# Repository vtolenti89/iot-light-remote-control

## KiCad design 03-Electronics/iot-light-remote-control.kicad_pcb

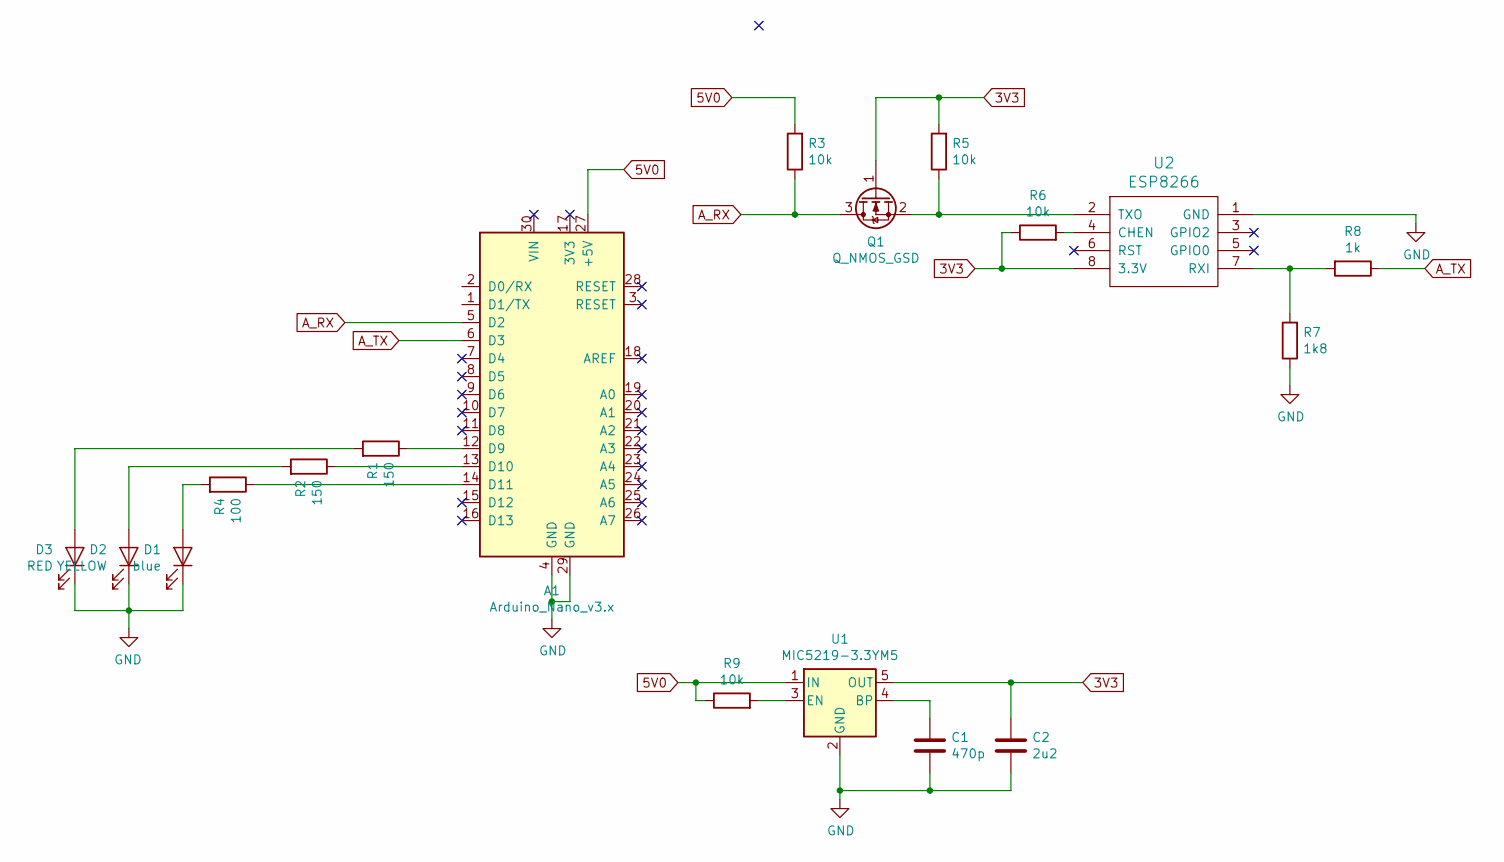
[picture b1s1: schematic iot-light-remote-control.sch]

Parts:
A1: Arduino_Nano_v3.x; Arduino_Nano
C1: 470p; C_0603_1608Metric_Pad1.05x0.95mm_HandSolder
C2: 2u2; C_0603_1608Metric_Pad1.05x0.95mm_HandSolder
D1: blue; LED_D5.0mm
D2: YELLOW; LED_D5.0mm
D3: RED; LED_D5.0mm
Q1: Q_NMOS_GSD; SOT-23
R1, R2: 150; R_0603_1608Metric_Pad1.05x0.95mm_HandSolder
R3, R5, R6, R9: 10k; R_0603_1608Metric_Pad1.05x0.95mm_HandSolder
R4: 100; R_0603_1608Metric_Pad1.05x0.95mm_HandSolder
R7: 1k8; R_0603_1608Metric_Pad1.05x0.95mm_HandSolder
R8: 1k; R_0603_1608Metric_Pad1.05x0.95mm_HandSolder
U1: MIC5219-3.3YM5; SOT-23-5
U2: ESP8266; PinHeader_2x04_P2.54mm_Vertical

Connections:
3V3: C2.1, Q1.1 (G), R5.2, R6.1, U1.5 (OUT), U2.8 (3.3V)
5V0: A1.27 (+5V), R3.2, R9.1, U1.1 (IN)
A_RX: A1.5 (D2), Q1.3 (D), R3.1
A_TX: A1.6 (D3), R8.1
GND: A1.4 (GND), A1.29 (GND), C1.2, C2.2, D1.1 (K), D2.1 (K), D3.1 (K), R7.1, U1.2 (GND), U2.1 (GND)
unnamed: A1.12 (D9), R1.1
unnamed: A1.13 (D10), R2.1
unnamed: A1.14 (D11), R4.1
unnamed: C1.1, U1.4 (BP)
unnamed: D1.2 (A), R4.2
unnamed: D2.2 (A), R2.2
unnamed: D3.2 (A), R1.2
unnamed: Q1.2 (S), R5.1, U2.2 (TXO)
unnamed: R6.2, U2.4 (CHEN)
unnamed: R7.2, R8.2, U2.7 (RXI)
unnamed: R9.2, U1.3 (EN)

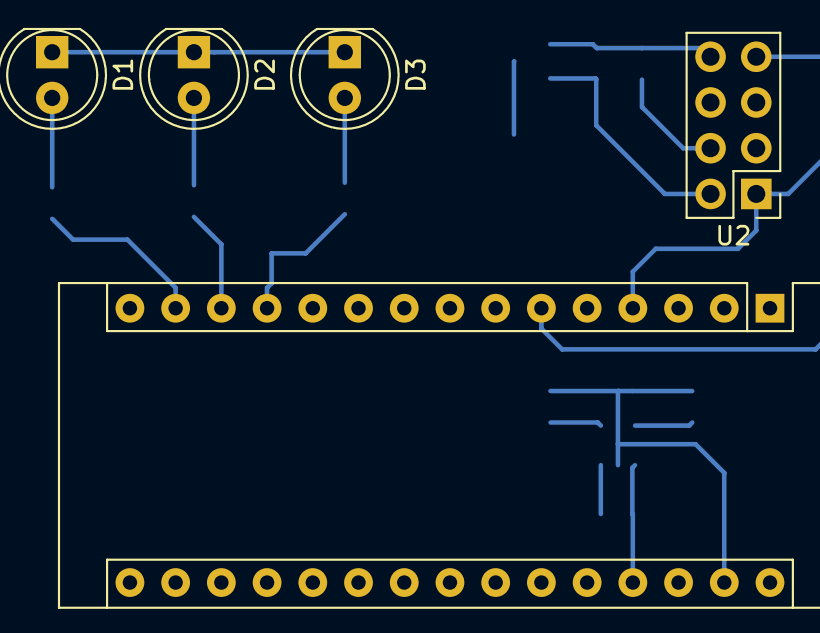
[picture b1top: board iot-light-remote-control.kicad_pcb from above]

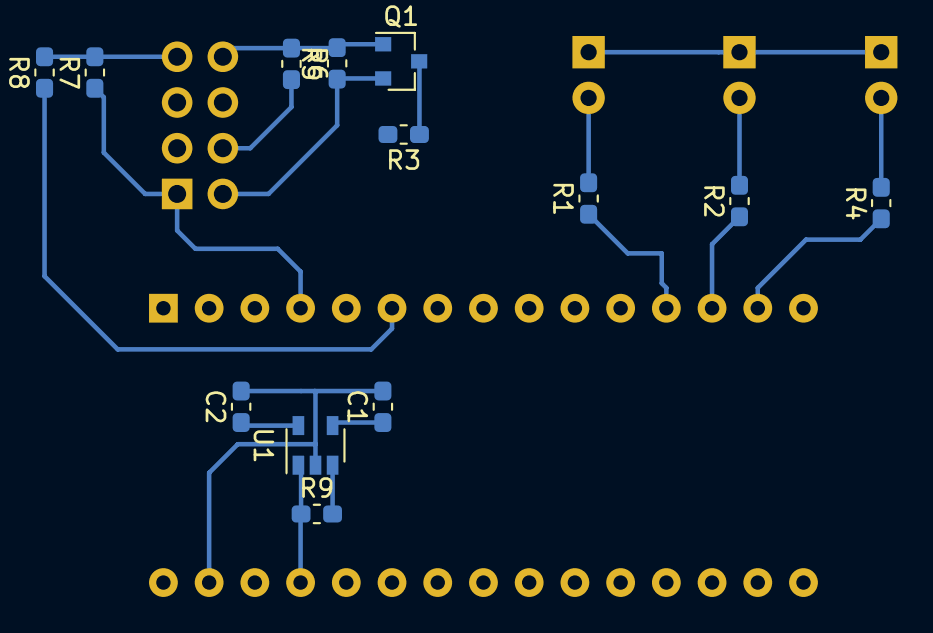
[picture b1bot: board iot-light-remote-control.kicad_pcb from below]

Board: 2 copper layers, 18 parts (13 on the bottom side), 16 nets.

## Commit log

2020-04-22 update firmware
2020-04-25 Update memory management of the firmware
2020-04-25 update mobile app routers
2020-04-26 update web app
2020-04-30 update webapp
2020-05-02 update interfaces
2020-05-03 update interface
2020-05-07 update web interface
2020-05-10 update swipe disabled
2020-09-08 update master
2021-01-06 Bump axios in /05-Software/iot-light-remote-control
    Bumps [axios](https://github.com/axios/axios) from 0.19.2 to 0.21.1.
    - [Release notes](https://github.com/axios/axios/releases)
    - [Changelog](https://github.com/axios/axios/blob/v0.21.1/CHANGELOG.md)
    - [Commits](https://github.com/axios/axios/compare/v0.19.2...v0.21.1)
